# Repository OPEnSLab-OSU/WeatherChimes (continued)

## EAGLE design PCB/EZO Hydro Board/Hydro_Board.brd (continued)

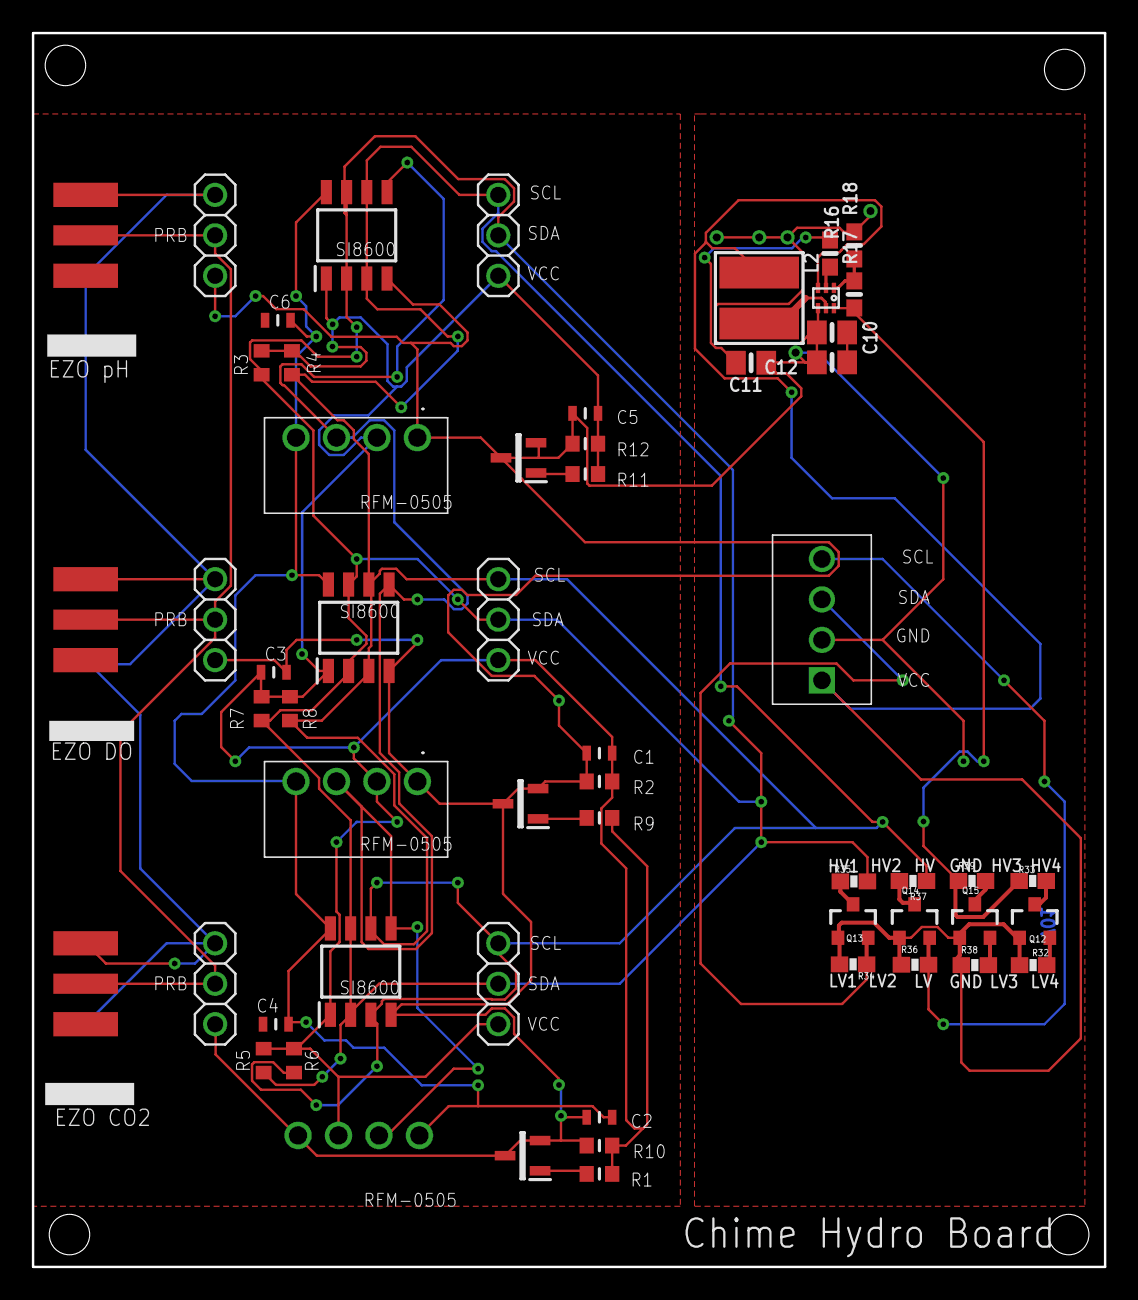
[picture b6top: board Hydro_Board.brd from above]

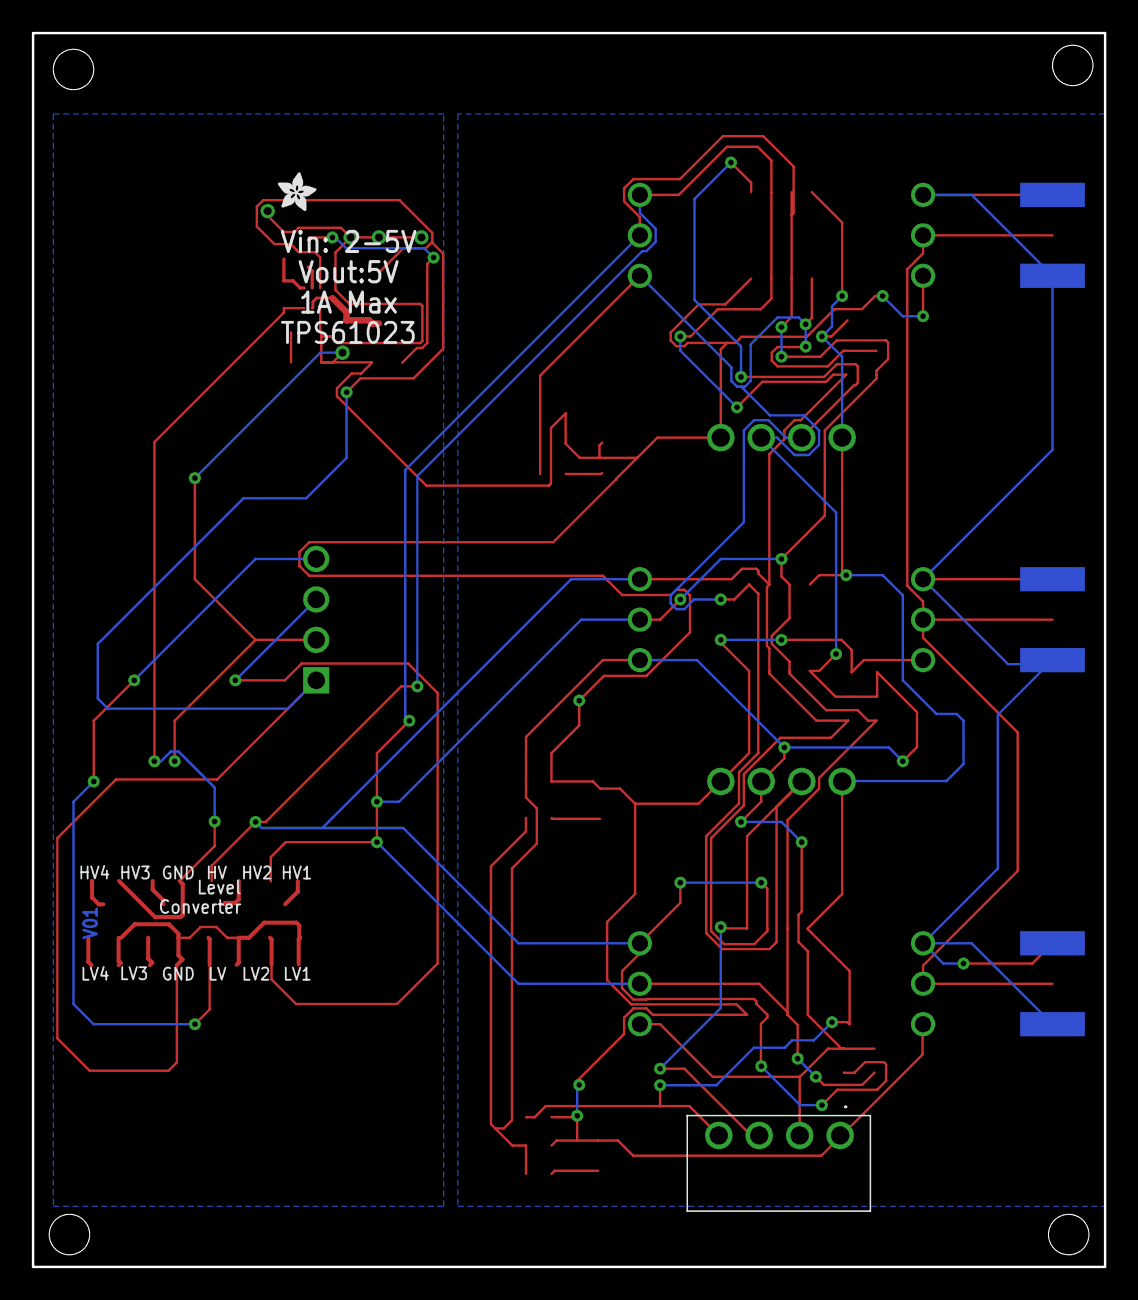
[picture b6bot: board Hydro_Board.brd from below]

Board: 2 copper layers, 67.3 x 77.5 mm, 58 parts (2 on the bottom side), 26 nets.

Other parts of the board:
U$33: ADAFRUIT_2.5MM

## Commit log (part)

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2021-09-10 Last working file using Adafruit.IO and MQTT
2021-09-10 Publishing Secrets file
2021-09-10 Arduino file with SDI12 dirty integration
    Used to test all hardware on WeatherChimes prototype, no Internet connectivity
2021-09-10 Connect to internet, only with Multiplexer
    Dirty Integration of device to HiveMQ. Uses a Multiplexer, and no SD card
2021-09-10 Combines previous commits into one file
    Full project functionality, all dirty integration. Next step is to implement this file into a publishing platform in Loom
2021-09-10 Node.js file to pass HiveMQ to MongodB
    This .js file is used to receive data from a HiveMQ MQTT broker and send it to a MongodB database. Needs to be hosted to allow for project functionality.
2021-09-10 Max patch that connects to MongodB database
    Listens to live updates of data in the database
2021-09-10 Secrets for Final_WeatherChimes
2021-09-10 Move location of MQTT_connect function into loop
2021-09-15 Minor formatting and commenting changes
2021-09-16 Add Loom Example
2021-09-16 Weathercomplete with MQTT.h file reference
2021-09-20 Update README.md
    Rough Draft- added some MQTT info, not finished
2021-09-20 Flow Chart
2021-09-20 Fixed faulting problem with sleep and MQTT internet. Changed some settings strings
2021-09-20 Update README.md
    Added more about WeatherChimes framework
2021-09-20 Update Pass.js, add error check and comments
2021-09-20 Update README.md
    More README updates
2021-09-20 Pass.js updates
2021-09-21 Update README.md
    Added a little about Max Patch
2021-09-21 Update README.md
    Final-ish README
2021-09-21 Update README.md
    More finalizing of info
2021-09-21 Update README.md
    More edits, added intro
2021-09-21 Cleaned up project after meeting with Chet
    Added a 5th entry for max patch and moved variables around in pass.js
2021-09-21 Update README.md
    Completed by
2021-09-24 Refactored MQTT settings into a secrets file used in the sketch rather than global variables in MQTT.h
2021-09-24 Removed secret info from arduino_secrets.h
2021-10-04 Removed redundant code directory
2021-10-26 Migrated WeatherChimes to using our manageable MQTT Broker
2021-11-04 Finalizing WeatherChimes
2021-11-09 Updated the script for handling data in Max
2021-11-22 Mostly finalized version WeatherChimes
2022-01-07 Up to date weather chimes
2022-01-19 Rolled back to working version of WeatherChimes. All 4 Chimes working
2022-01-28 Cleaned up and finalized WeataherChimes, for use with CERN
2022-01-28 Removed line break before wiki
2022-01-31 WiFi low-power state, fixed config.h
2022-02-01 Create Base Plate
2022-02-01 Create HypnosAssembly
2022-02-15 Rolled back code to a seemingly stable version running on Chime4 for Chet's class
2022-04-03 Cleaned up code and added README's
2022-04-07 Modified MongoDB node-red node
2022-04-14 Added mosquitto.conf
2022-04-28 Removed Opens MongoDB cluster from node-red flows
2022-04-28 Images for Node-RED README.md
2022-06-08 Added MQTT Deps.
2022-06-08 Moved ArduinoMQTTClient to Dependencies
2022-06-29 Uploaded fixed topic code
2022-07-19 Coverted WeatherChimes to Loom V4
2022-07-19 Updated node-red
2022-07-19 updated secrets
2022-07-23 Switched to loading all creds from SD
2022-08-01 Added database name to mqtt_creds.json
2022-10-10 Updated WeatherChimes code to the latest stable version
2022-10-10 Stable for Sitka deployment
2022-10-19 Create ChimeV1
2022-10-24 Create xxx
2022-11-10 Create xx
2022-11-14 Uploaded old weatherchimes code
2022-11-14 Rename WeatherChimesV4SDSleepMQTT.ino to WeatherChimes.ino
2022-11-14 New code running on an old device
2023-01-07 Create poster
2023-01-09 Create 2022
2023-01-09 Create x
2023-01-12 Add files via upload
    updated figure
2023-03-07 Gerber files
2023-03-16 schematic pdf
2023-04-09 Add files via upload
    adaptor board
2023-04-10 Air Wiring Issue resolved
2023-05-16 Redesign of Chime v2.1. Made it smaller and added LEDs to solar charger circuit
2023-05-16 EZO WeatherChime Adapter Board v1
2023-05-16 Label Update
2023-05-17 Added LEDs
2023-05-17 Component label
2023-05-17 GND Air Wires
2023-05-17 All air wires good
2023-05-18 Final touches
2023-06-06 Final EZO Hydrology Adapter Board
2023-06-06 Edited labels
2023-07-11 Create EZO_Expansion
2023-07-31 WeatherChimesv2.6 files from Google Drive
2023-08-07 EZO single board files
2023-08-15 BRD file
2023-08-15 SCH File
2023-08-16 PCB Fixes for 3-probe expansion brd
2023-08-16 removing old files
2023-08-18 Update README.md with operations manual
2023-09-20 Adding final I2C_Extender and Chime PCB board file
2023-12-01 Tied the OFF Pin on the EZO Isolated Carrier board to high, hopefully fixing our issues of fried DO circuits
